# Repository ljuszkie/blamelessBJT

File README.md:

# blamelessBJT

Audio power amplifier based on Self's blameless amplifier

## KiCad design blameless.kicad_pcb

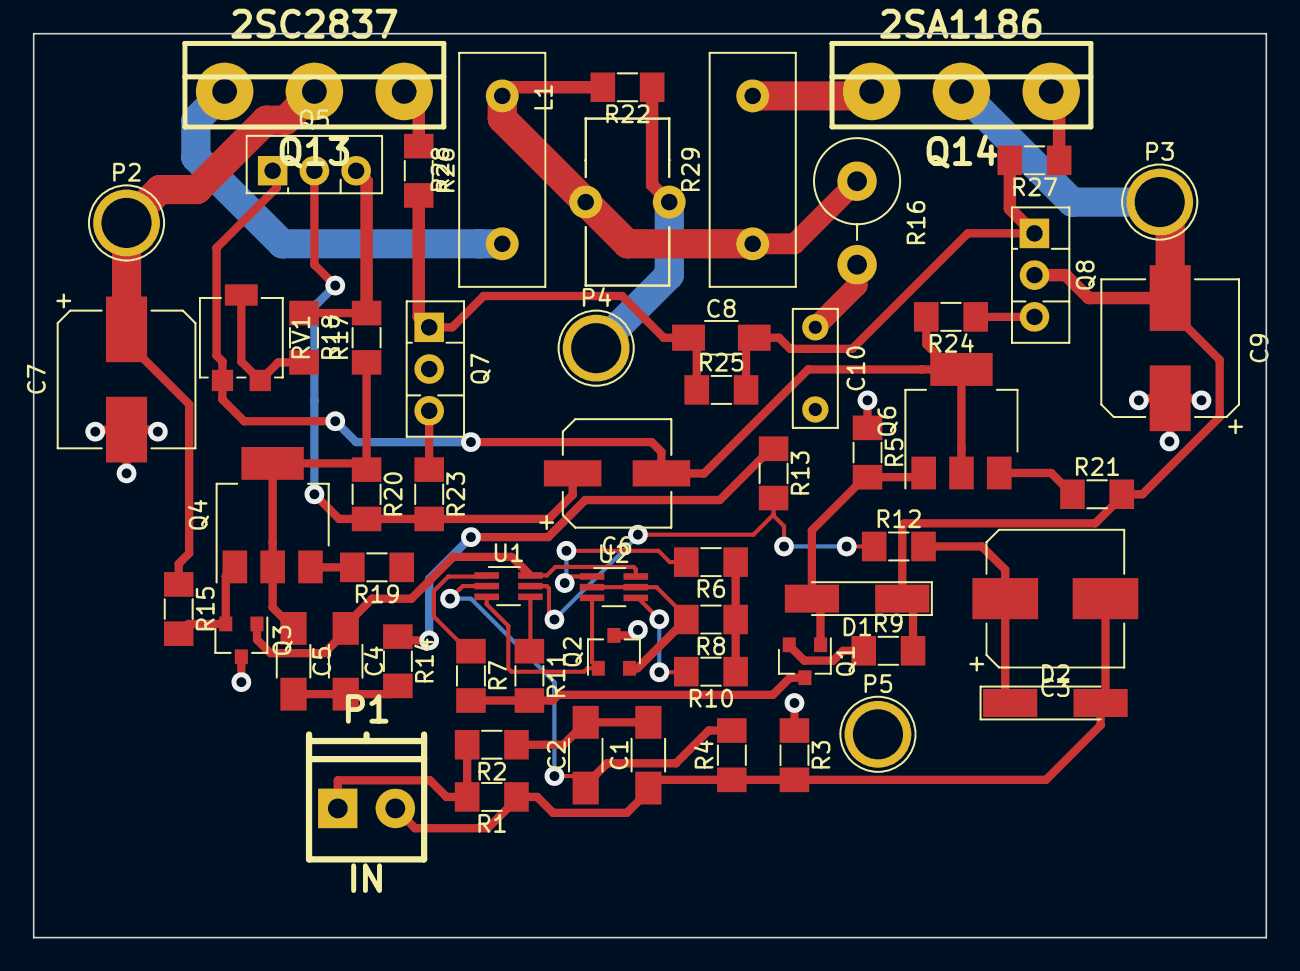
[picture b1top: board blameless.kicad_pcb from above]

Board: 2 copper layers, 75.0 x 55.0 mm, 60 parts (0 on the bottom side), 39 nets.

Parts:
C1, C5: 220p; C_1206_HandSoldering
C2: 4u7; C_1206_HandSoldering
C3, C7, C9: 220u 35V; CP_Elec_8x10
C4: 82p; C_1206_HandSoldering
C6: 47u 35V; CP_Elec_6.3x7.7
C8: 10u; C_1206_HandSoldering
C10: 100n; C_Rect_L7.0mm_W2.5mm_P5.00mm
D1: 8V2; D_MiniMELF_Handsoldering
D2: DL4148; D_MiniMELF_Handsoldering
L1: 100n; Choke_Toroid_5x10mm_Vertical
P1: IN; pt_1,5-2-3,5-h
P2: VCC; 1pin
P3: VEE; 1pin
P4: OUT; 1pin
P5: GND; 1pin
Q1: BC850C; SOT-23
Q2: BC857; SOT-23
Q3: BC860C; SOT-23
Q4: BF723; SOT-223-3_TabPin2
Q5: BD135; TO-126_Vertical
Q6: BCP54; SOT-223-3_TabPin2
Q7: BD135; TO-126-3_Vertical
Q8: BD140; TO-126-3_Vertical
Q13: 2SC2837; to247
Q14: 2SA1186; to247
R1: 100k; R_MiniMELF_MMA-0204
R2: 2k2; R_MiniMELF_MMA-0204
R3, R22, R23, R24: 10R; R_MiniMELF_MMA-0204
R4, R13: 22k; R_MiniMELF_MMA-0204
R5: 4k7; R_MiniMELF_MMA-0204
R6, R7, R10, R11: 200R; R_MiniMELF_MMA-0204
R8: 10k; R_MiniMELF_MMA-0204
R9, R12: 1k2; R_MiniMELF_MMA-0204
R14: 2k; R_MiniMELF_MMA-0204
R15, R19, R21: 470R; R_MiniMELF_MMA-0204
R16: 10R; R_Axial_DIN0516_L15.5mm_D5.0mm_P5.08mm_Vertical
R17: 1k; R_MiniMELF_MMA-0204
R18: 220R; R_MiniMELF_MMA-0204
R20: 16R; R_MiniMELF_MMA-0204
R25: 68R; R_MiniMELF_MMA-0204
R26, R27: 2R2; R_MiniMELF_MMA-0204
R28, R29: 0R22; R_Box_L14.0mm_W5.0mm_P9.00mm
RV1: 1k; Potentiometer_Bourns_3214G_Horizontal
U1: BCM847; SOT-363_SC-70-6_Handsoldering
U2: BCM857; SOT-363_SC-70-6_Handsoldering

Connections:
/IN: P1.1, R1.2, R2.2
/out: L1.2, R13.1, R14.1, R16.1, R22.2, R28.2, R29.1
GND: C7.2, C9.1, C10.2, P5.1, Q2.3, Q3.3, R3.1, R5.1
GNDREF: C1.1, C3.2, D2.2, P1.2, R1.1, R3.2, R4.1
unnamed: C1.2, C2.2, R2.1
unnamed: C2.1, R4.2, U1.2
unnamed: C3.1, D2.1, R12.2
unnamed: C4.1, Q3.1, U1.6, U2.6
unnamed: C4.2, C5.2, R14.2
unnamed: C5.1, Q4.2, R17.1, R20.1
unnamed: C6.1, Q5.2, R20.2, R23.2
unnamed: C6.2, Q5.1, Q6.2, R24.2, RV1.3
unnamed: C8.1, Q7.1, R25.1, R26.2
unnamed: C8.2, Q8.1, R25.2, R27.2
unnamed: C10.1, R16.2
unnamed: D1.2, Q1.1, Q6.1, R5.2
unnamed: L1.1, P4.1, R22.1
unnamed: Q1.2, R9.1
unnamed: Q1.3, R7.2, R11.2
unnamed: Q2.1, U1.3, U2.3
unnamed: Q2.2, R8.2, U2.2, U2.5
unnamed: Q3.2, Q4.1, R15.2
unnamed: Q4.3, R19.2
unnamed: Q5.3, R17.2, R18.1
unnamed: Q6.3, R21.1
unnamed: Q7.3, R23.1
unnamed: Q8.3, R24.1
unnamed: Q13.1, R26.1
unnamed: Q13.3, R28.1
unnamed: Q14.1, R27.1
unnamed: Q14.3, R29.2
unnamed: R6.2, U2.1
unnamed: R7.1, U1.1
unnamed: R10.2, U2.4
unnamed: R11.1, U1.4
unnamed: R12.1, R13.2, U1.5
unnamed: R18.2, RV1.1, RV1.2
VCC: C7.1, P2.1, Q7.2, Q13.2, R6.1, R8.1, R10.1, R15.1, R19.1
VEE: C9.2, D1.1, P3.1, Q8.2, Q14.2, R9.2, R21.2

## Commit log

2022-11-24 Added LTSpice simulation
2023-04-10 Move to KiCAD 7
